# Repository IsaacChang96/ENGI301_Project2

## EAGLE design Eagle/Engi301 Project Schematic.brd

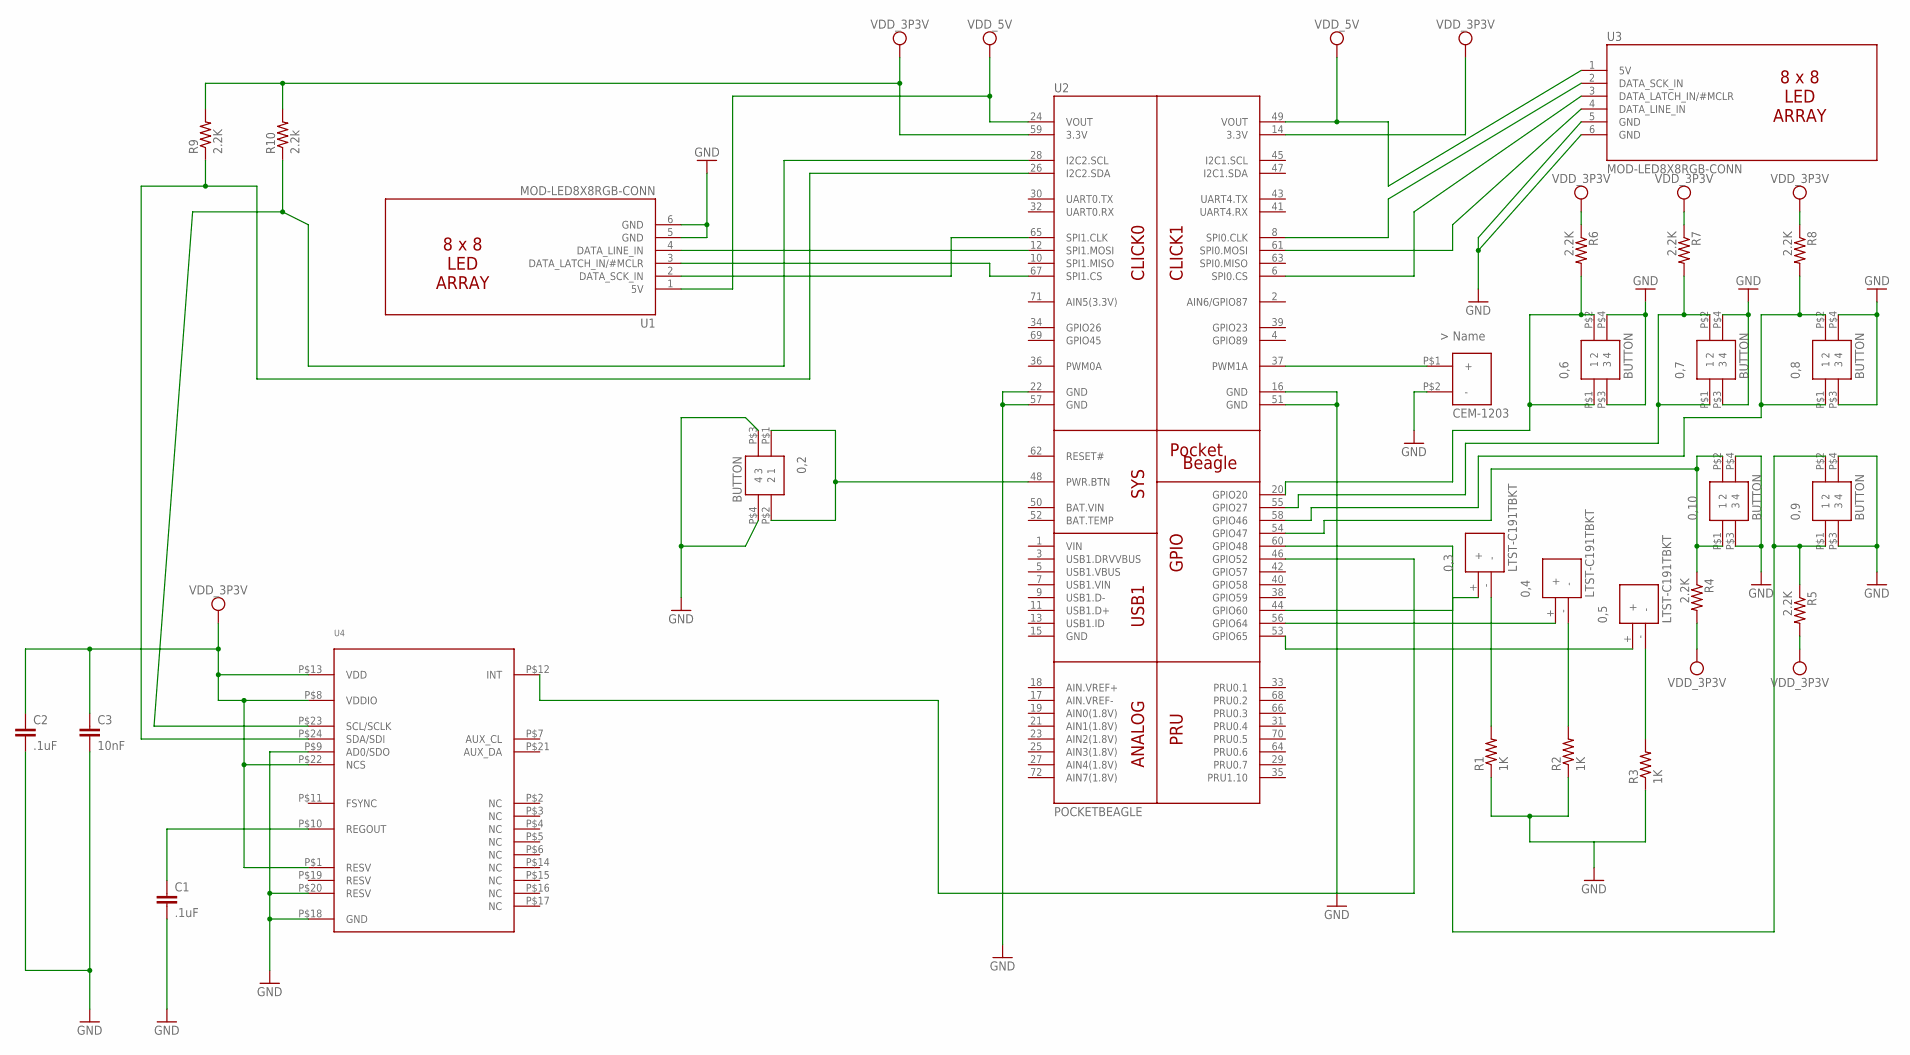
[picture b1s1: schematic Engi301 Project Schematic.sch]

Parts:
0,1: CEM-1203
0,2, 0,6, 0,7, 0,8, 0,9, 0,10: BUTTON
0,3, 0,4, 0,5: LTST-C191TBKT; LTST_C191TBKT
C1, C2: .1uF; C0603
C3: 10nF; C0402
R1, R2, R3: 1K; R0603
R4, R5, R6, R7, R8, R9: 2.2K; R0603
R10: 2.2k; R0603
U1, U3: MOD-LED8X8RGB-CONN; FE06W
U2: POCKETBEAGLE
U4: MPU-9250; QFN_3MMX3MM

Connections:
GND: 0,1.P$2 (-), 0,2.P$3 (3), 0,2.P$4 (4), 0,6.P$3 (3), 0,6.P$4 (4), 0,7.P$3 (3), 0,7.P$4 (4), 0,8.P$3 (3), 0,8.P$4 (4), 0,9.P$3 (3), 0,9.P$4 (4), 0,10.P$3 (3), 0,10.P$4 (4), C1.2, C2.2, C3.2, R1.1, R2.1, R3.1, U1.5 (GND), U1.6 (GND), U2.16 (GND), U2.22 (GND), U2.51 (GND), U2.57 (GND), U3.5 (GND), U3.6 (GND), U4.P$9 (AD0/SDO), U4.P$18 (GND), U4.P$20 (RESV)
unnamed: R10.1, U2.28 (I2C2.SCL), U4.P$23 (SCL/SCLK)
unnamed: U2.8 (SPI0.CLK), U3.2 (DATA_SCK_IN)
unnamed: U2.61 (SPI0.MOSI), U3.4 (DATA_LINE_IN)
unnamed: C1.1, U4.P$10 (REGOUT)
unnamed: 0,5.+, U2.53 (GPIO65)
unnamed: U1.2 (DATA_SCK_IN), U2.65 (SPI1.CLK)
unnamed: U1.4 (DATA_LINE_IN), U2.12 (SPI1.MOSI)
unnamed: U1.3 (DATA_LATCH_IN/#MCLR), U2.67 (SPI1.CS)
unnamed: 0,4.+, U2.56 (GPIO64)
unnamed: 0,3.+, U2.44 (GPIO60)
unnamed: 0,1.P$1 (+), U2.37 (PWM1A)
unnamed: U2.46 (GPIO52), U4.P$12 (INT)
unnamed: 0,2.P$1 (1), 0,2.P$2 (2), U2.48 (PWR.BTN)
unnamed: 0,3.-, R1.2
unnamed: 0,4.-, R2.2
unnamed: 0,5.-, R3.2
unnamed: U2.6 (SPI0.CS), U3.3 (DATA_LATCH_IN/#MCLR)
unnamed: R9.1, U2.26 (I2C2.SDA), U4.P$24 (SDA/SDI)
unnamed: 0,6.P$1 (1), 0,6.P$2 (2), R6.2, U2.20 (GPIO20)
unnamed: 0,7.P$1 (1), 0,7.P$2 (2), R7.2, U2.55 (GPIO27)
unnamed: 0,8.P$1 (1), 0,8.P$2 (2), R8.2, U2.58 (GPIO46)
unnamed: 0,10.P$1 (1), 0,10.P$2 (2), R4.1, U2.54 (GPIO47)
unnamed: 0,9.P$1 (1), 0,9.P$2 (2), R5.1, U2.60 (GPIO48)
SYS_VDD1_3P3V: C2.1, C3.1, R4.2, R5.2, R6.1, R7.1, R8.1, R9.2, R10.2, U2.14 (3.3V), U2.59 (3.3V), U4.P$1 (RESV), U4.P$8 (VDDIO), U4.P$13 (VDD), U4.P$22 (NCS)
SYS_VDD_5V: U1.1 (5V), U2.24 (VOUT), U2.49 (VOUT), U3.1 (5V)

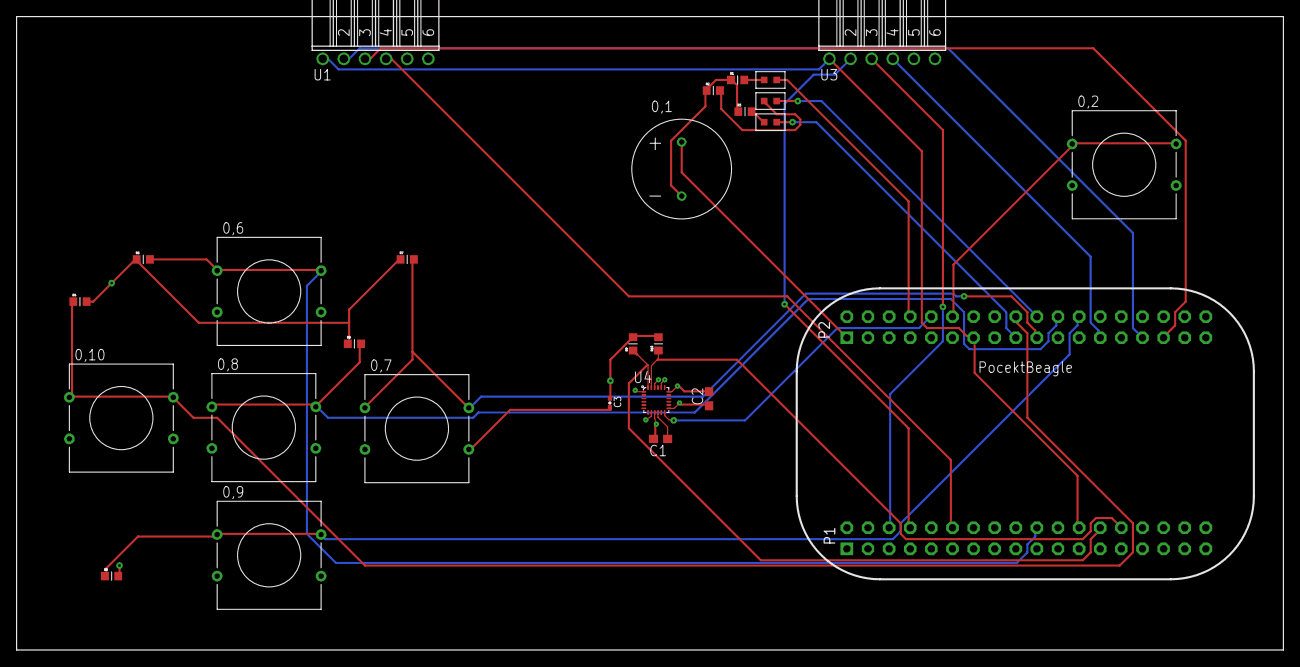
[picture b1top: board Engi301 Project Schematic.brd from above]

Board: 4 copper layers, 152.4 x 76.2 mm, 27 parts (0 on the bottom side), 26 nets.

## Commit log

2018-04-16 Initial Library Commit
2018-04-20 schematic and board files
2018-04-22 gerber files for board
